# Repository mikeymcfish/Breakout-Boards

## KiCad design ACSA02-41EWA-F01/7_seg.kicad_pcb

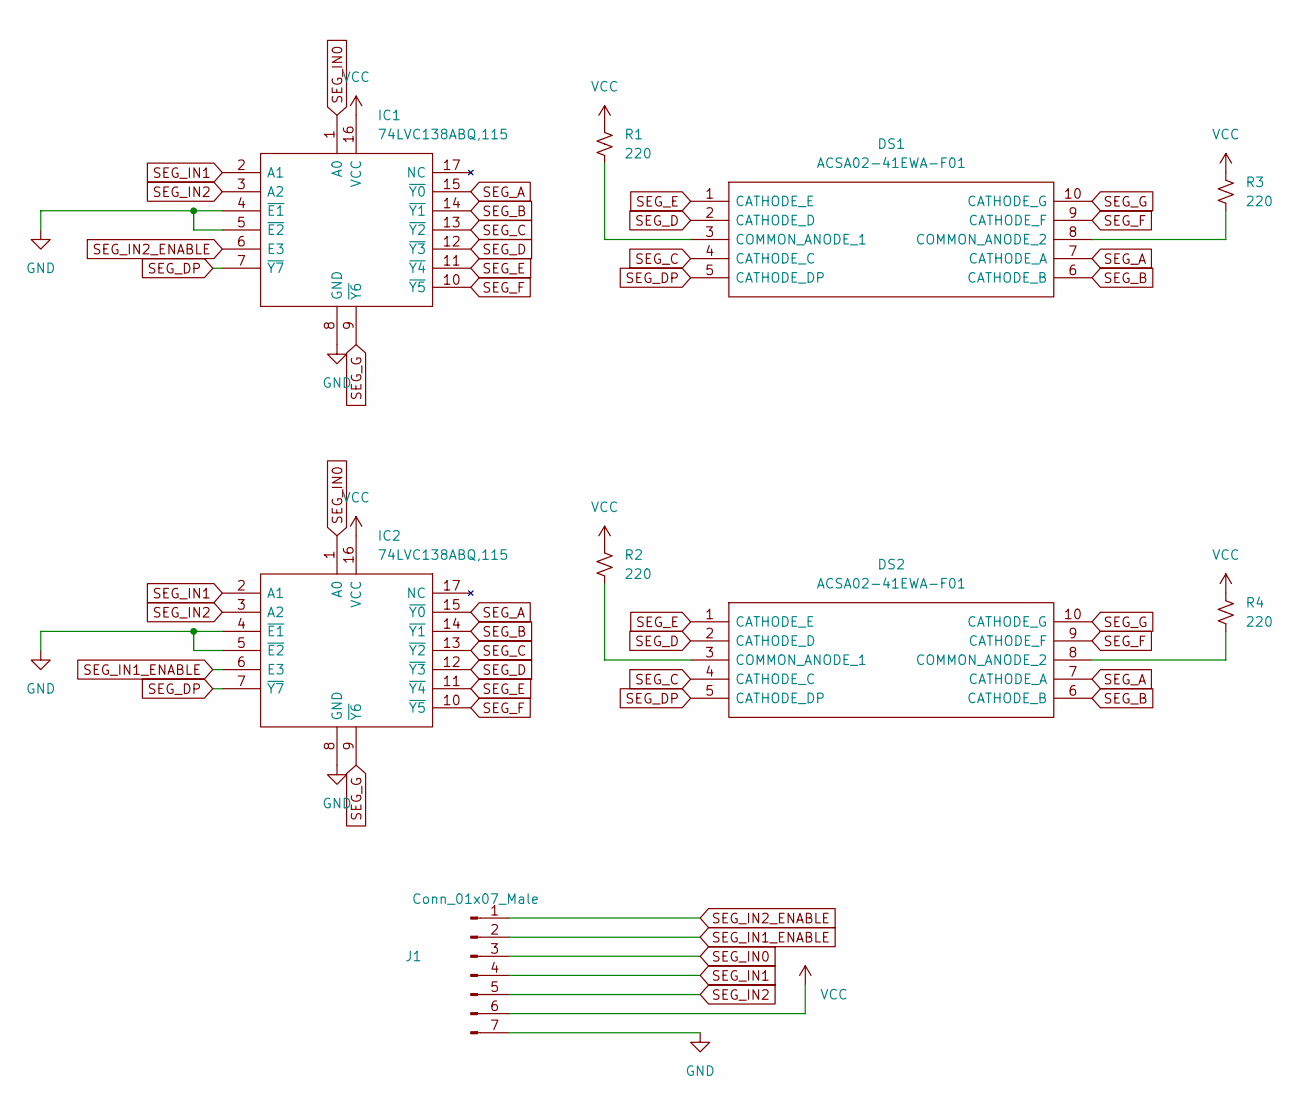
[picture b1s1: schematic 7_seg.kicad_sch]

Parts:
DS1, DS2: ACSA02-41EWA-F01; ACSA0241EWAF01; Mouser Part Number 604-ACSA02-41EWA
IC1, IC2: 74LVC138ABQ,115; 74AHCT595BQ115; Mouser Part Number 771-LVC138ABQ115
J1: Conn_01x07_Male; PinHeader_1x07_P2.54mm_Vertical
R1, R2, R3, R4: 220; R_1206_3216Metric

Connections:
GND: IC1.4 (~E1), IC1.5 (~E2), IC1.8 (GND), IC2.4 (~E1), IC2.5 (~E2), IC2.8 (GND), J1.7
unnamed: DS1.3 (COMMON_ANODE_1), R1.2
unnamed: DS1.8 (COMMON_ANODE_2), R3.2
unnamed: DS2.3 (COMMON_ANODE_1), R2.2
unnamed: DS2.8 (COMMON_ANODE_2), R4.2
SEG_A: DS1.7 (CATHODE_A), DS2.7 (CATHODE_A), IC1.15 (~Y0), IC2.15 (~Y0)
SEG_B: DS1.6 (CATHODE_B), DS2.6 (CATHODE_B), IC1.14 (~Y1), IC2.14 (~Y1)
SEG_C: DS1.4 (CATHODE_C), DS2.4 (CATHODE_C), IC1.13 (~Y2), IC2.13 (~Y2)
SEG_D: DS1.2 (CATHODE_D), DS2.2 (CATHODE_D), IC1.12 (~Y3), IC2.12 (~Y3)
SEG_DP: DS1.5 (CATHODE_DP), DS2.5 (CATHODE_DP), IC1.7 (~Y7), IC2.7 (~Y7)
SEG_E: DS1.1 (CATHODE_E), DS2.1 (CATHODE_E), IC1.11 (~Y4), IC2.11 (~Y4)
SEG_F: DS1.9 (CATHODE_F), DS2.9 (CATHODE_F), IC1.10 (~Y5), IC2.10 (~Y5)
SEG_G: DS1.10 (CATHODE_G), DS2.10 (CATHODE_G), IC1.9 (~Y6), IC2.9 (~Y6)
SEG_IN0: IC1.1 (A0), IC2.1 (A0), J1.3
SEG_IN1: IC1.2 (A1), IC2.2 (A1), J1.4
SEG_IN1_ENABLE: IC2.6 (E3), J1.2
SEG_IN2: IC1.3 (A2), IC2.3 (A2), J1.5
SEG_IN2_ENABLE: IC1.6 (E3), J1.1
VCC: IC1.16 (VCC), IC2.16 (VCC), J1.6, R1.1, R2.1, R3.1, R4.1

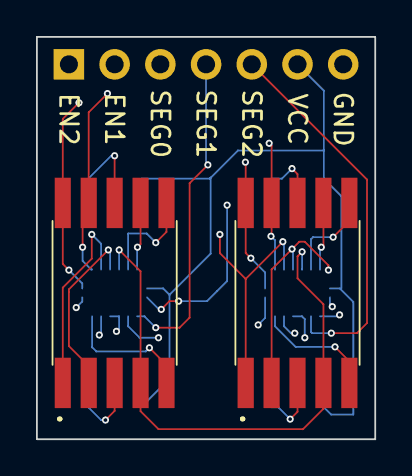
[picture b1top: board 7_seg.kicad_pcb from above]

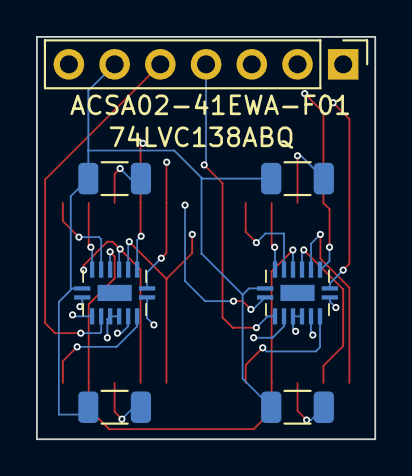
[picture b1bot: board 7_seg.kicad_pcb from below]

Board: 4 copper layers, 18.8 x 22.4 mm, 9 parts (7 on the bottom side), 19 nets.

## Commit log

2022-04-20 init
    Code for single 7-segment
